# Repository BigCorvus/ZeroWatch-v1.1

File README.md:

# ZeroWatch-v1.1

**Replacement board for a cheap chinese U8/U80 watch.**  
Based on the work of Dan Geiger.
Features:<br />
- ATSAMD21 microcontroller with Arduino support via USB bootloader<br />
- capacitive touchscreen (based on the BL6280 controller)<br />
- HM11 bluetooth 4.0 module with amputated PCB antenna and primitive coax dipole instead<br />
- ST7735 128x128 18-pin SPI tft (the one that's inside the watch already)<br />
- MPU9250 9-DOF IMU<br />
- BME680 environmental sensor<br />
- vibration motor. I decided to go with https://de.aliexpress.com/item/Free-shipping-100pcs-lot-4-10-MM-Ultra-Micro-Vibration-Motor-Rotor-motor-DC-Massager-motor/32748925343.html?spm=a2g0s.9042311.0.0.27424c4dg2oSdt as the vibration motor to save space for a bigger battery.<br />
- infrared transmitter (APA3010F3C-GX LED)<br />
- piezo disc (optional)<br />
- I equipped mine with a QI inductive charging pad<br />

The software is based on Dan Geigers ingenious menu structure which enables you to add new apps easily.
It's quite raw and buggy but demonstrates most features and is optimized for power consumption. With the 403030 lipo I can get 8 days of standby time with bluetooth constantly advertising and the ATSAMD21's inbuilt RTC running.<br />

**Some tips if you want to repeat the project:**  
- The cheapest versions of the U8 (there are even ones below 10$, a great contribution to a healthy environment!) are usually so stripped-down that they are not useful anymore! They have their capacitive touch controller on the main PCB an not on a flex-rigid assembly. I found the U80 by NAIKU to be a good hacking victim. Search this on Aliexpress. Its design is slightly different to the U8 from the outside but from the inside everything fits. Note: the U8 by the same brand is useless.  
  
The pic shows some useless variants on the right and some hackable ones on the left (with their 6pin FPC connectors desoldered for the most part). As you can see,on the useless variants there's no touch controller on the ribbon cable but a 15pin FPC connector with nothing but the traces to the glass. Also, v1.0 and v1.2's bare PCB are depicted on the very left ;)  

- Finding a proper screen might be a problem. 18 pin versions of the 1.44'' ST7735/ILI9163 screen with the right dimensions are rare. In fact I've only found one source: https://de.aliexpress.com/item/Maithoga-1-44-zoll-18-PIN-SPI-TFT-LCD-St7735-Stick-IC-128RGB-128/32843155779.html?spm=a2g0s.9042311.0.0.27424c4d3j1YYo. Some screens found in the cheap U8/U80 watches have weird controller settings and dispay inverted colors or don't show the small fonts so be aware. You might need to buy several differen variants. Note: only 14 of the 18 pins have to be soldered to the PCB.  
- some modifications on the enclosure are needed. In order to accommodate the v1.1 board you have to cut away the plastic brackets that surround the microphone. This is best done usind electronics side cutters. Some other plastic tabs might need to be removed depending on the variant you have. But the enclosures are surprisingly similar with few variations between versions.  
- The button can be installed either using the native one or by installing a SW1256CT-ND switch (digikey). The latter requires some hacking to the enclosure  
- a small hole has to be drilled for the IR LED if you wish to use one.
- the HM-11 should be flashed with the newest firmware before installing on the v1.1 PCB.   
- if you have a PCB manufactured, the substrate thickness should be between 0.4 and 0.8mm, so OSH Park's 0.8mm service is a good choice.
- in the latest modification I replaced the HM11 with a tiny nRF52832 module (https://de.aliexpress.com/item/32840369737.html?spm=a2g0o.productlist.0.0.22d43589wkmK8l&s=p&algo_pvid=c23bce47-e7e4-404d-a416-df6c4eb9f3a8&algo_expid=c23bce47-e7e4-404d-a416-df6c4eb9f3a8-1&btsid=25448c7b-c97c-4e22-b295-2b7a35d97857&ws_ab_test=searchweb0_0%2Csearchweb201602_8%2Csearchweb201603_53) which I  flashed with a modified BLE UART example inside the Adafruit nRF52 core. It can be brought into sub-µA deep sleep by the ATSAMD. By using a passthrough sketch for the ATSAMD which lets it act as an USB-to UART bridge you can even program the nRF52832 via USB and the Arduino IDE. I tested the concept and it seems to be the best solution so far. Code and wiring scheme for this will be puplished as soon as I have time for it.

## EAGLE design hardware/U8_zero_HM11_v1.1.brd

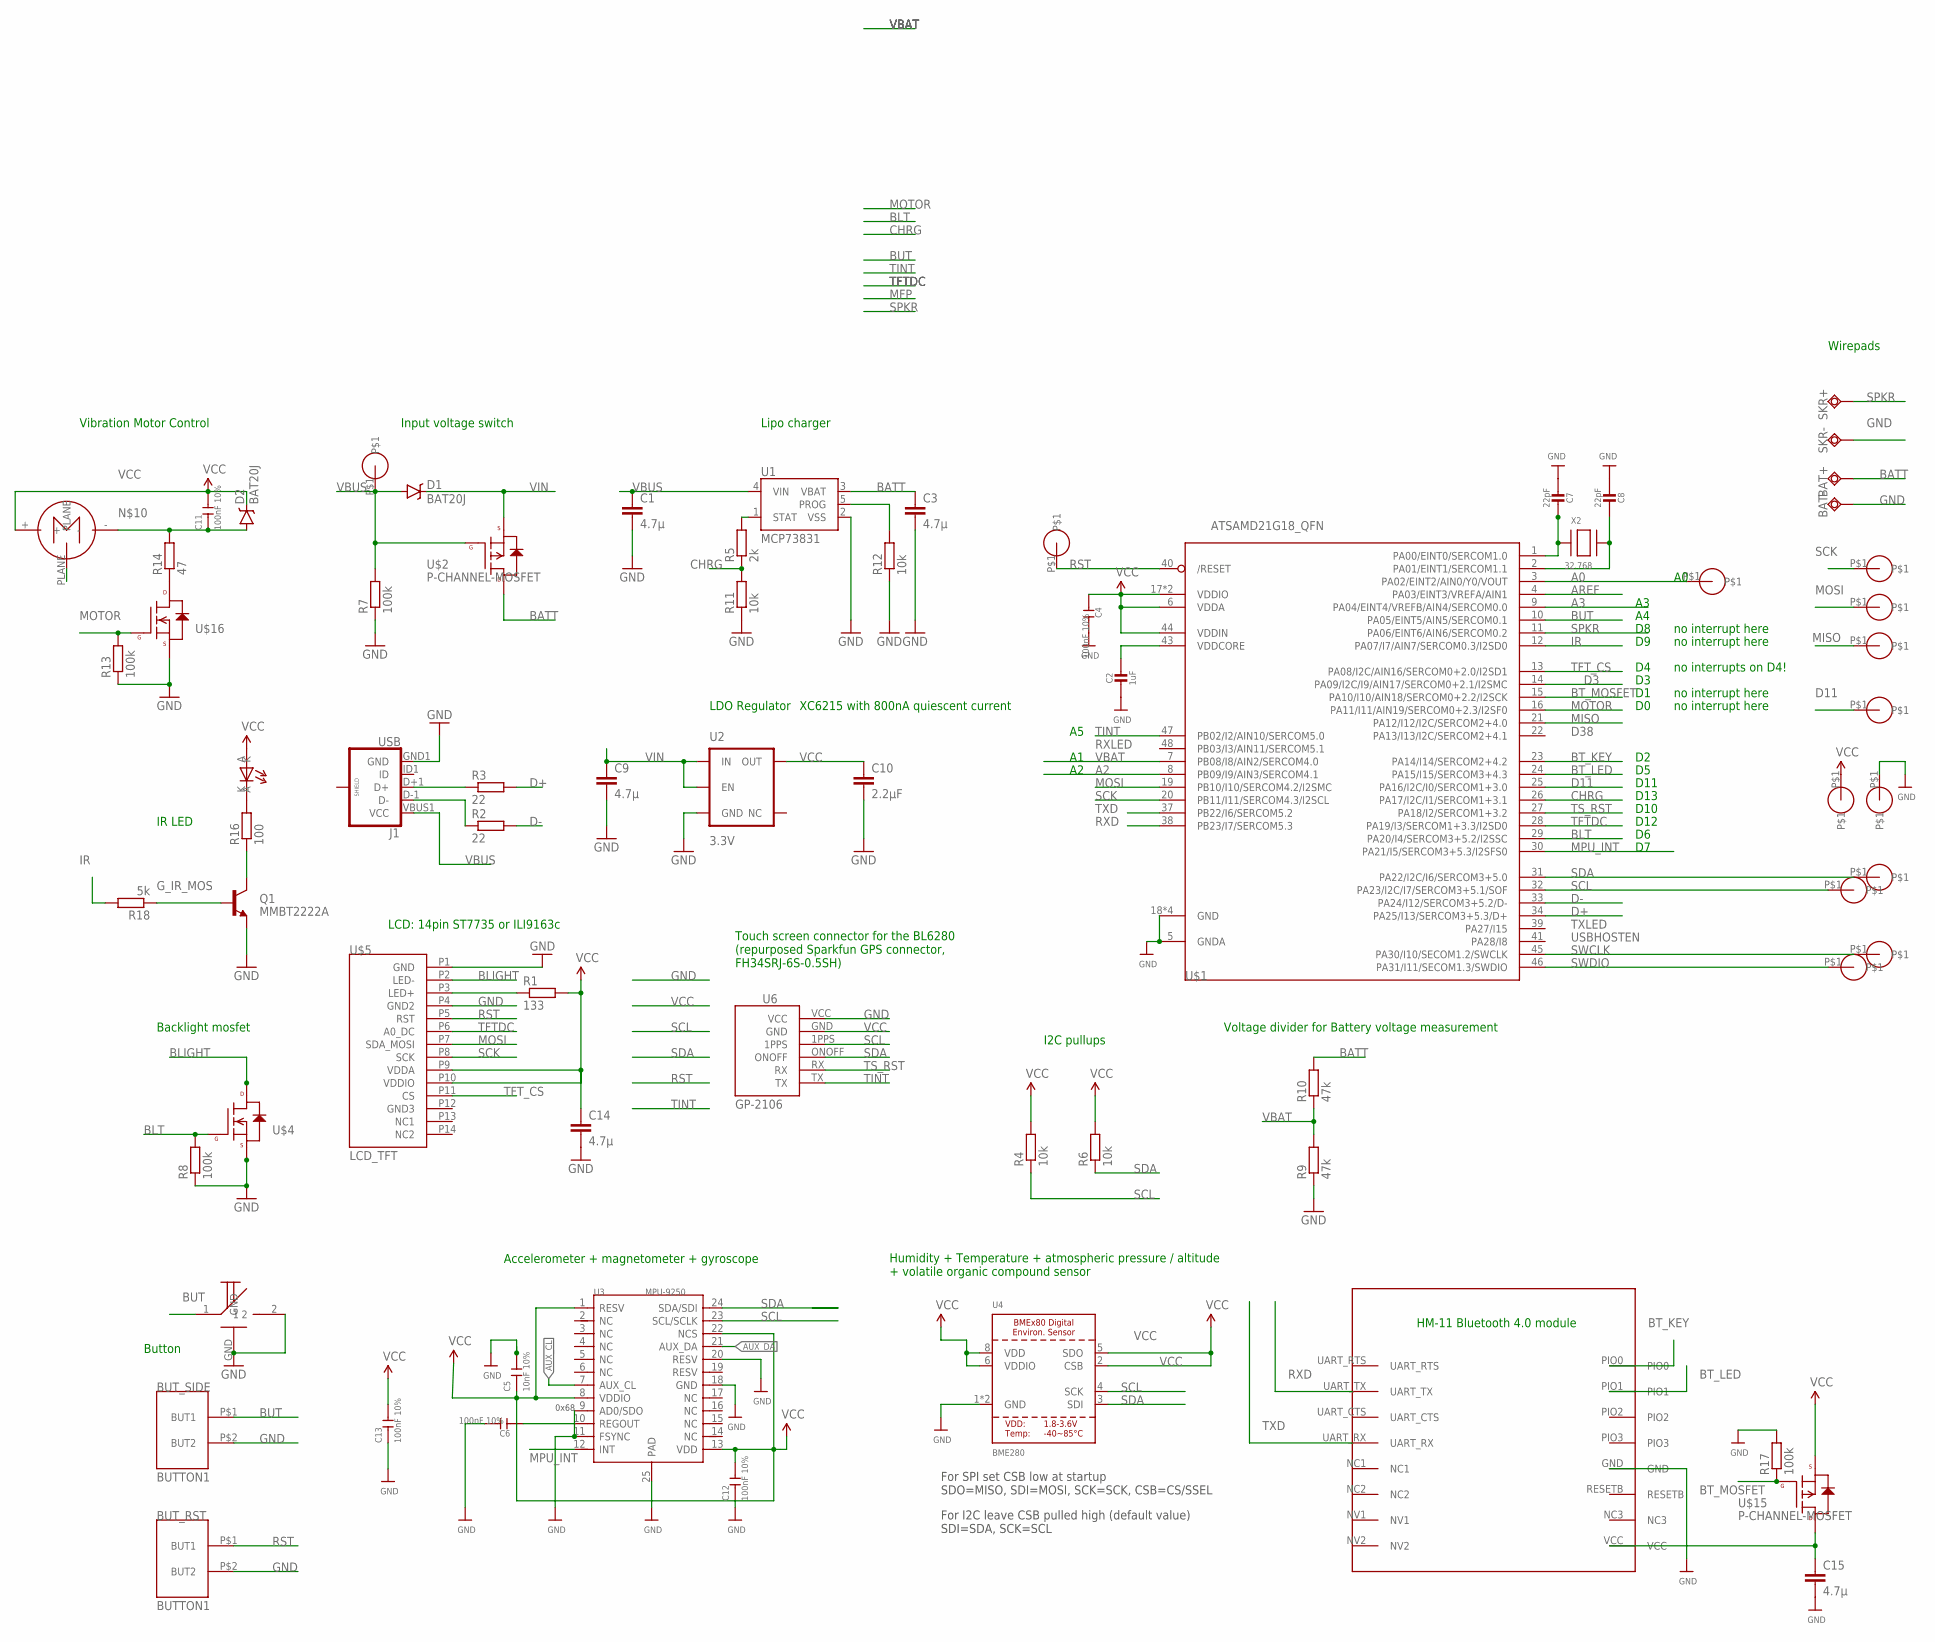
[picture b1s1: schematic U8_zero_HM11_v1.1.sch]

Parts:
BAT+: TPSQTP16R; TP16R
BAT-: TPSQTP16R; TP16R
BUT_RST: BUTTON1
BUT_SIDE: BUTTON1
C1, C3, C9, C14, C15: 4.7µ; C0603
C2: 1uF; 0603-NO
C4, C6, C11, C12, C13: 100nF 10%; C0603
C5: 10nF 10%; C0603
C7, C8: 22pF; 0603-NO
C10: 2.2µF; C0603
CLK: MINIPAD
D1, D2: BAT20J; SOD-323
DIO, DIO1, DIO2, DIO3, DIO4, DIO5: MINIPAD
J1: USB; USB-B-MICRO-SMD_V03
Q1: MMBT2222A; SOT23-3
R1: 133; R0603
R2, R3: 22; R0603
R4, R6, R11, R12: 10k; R0603
R5: 2k; R0603
R7, R8, R13, R17: 100k; R0603
R9, R10: 47k; R0603
R14: 47; R0603
R16: 100; R0603
R18: 5k; R0603
SKR+: TPSQTP12R; TP12R
SKR-: TPSQTP12R; TP12R
U1: MCP73831; SOT23-5
U2: 3.3V; SOT23-5
U3: MPU-9250; LEAD-QFN24
U4: BME280
U6: GP-2106
U$1: ATSAMD21G18_QFN; TQFN48_7MM
U$2, U$15: P-CHANNEL-MOSFET; SOT23-3
U$3, U$18, U$20, U$21, U$41, U$42: MINIPAD
U$4, U$16: N-CHANNEL-MOSFET-BSS138; SOT23-3
U$5: LCD_TFT; LCD_FPC14
U$8: HM-11
U$22: B3U-3100P-B
U$23: VIBRO
U$24: APA3010F3C-GX
X2: 32.768; XTAL3215

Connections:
A0: U$1.3 (PA02/EINT2/AIN0/Y0/VOUT), U$20.P$1
A2: U$1.8 (PB09/I9/AIN3/SERCOM4.1)
A3: U$1.9 (PA04/EINT4/VREFB/AIN4/SERCOM0.0)
AREF: U$1.4 (PA03/EINT3/VREFA/AIN1)
AUX_CL: U3.7 (AUX_CL)
AUX_DA: U3.21 (AUX_DA)
BATT: BAT+.TP, C3.1, R10.2, U1.3 (VBAT), U$2.3 (D)
BLIGHT: U$4.3 (D), U$5.P2 (LED-)
BLT: R8.2, U$1.29 (PA20/I4/SERCOM3+5.2/I2SSC), U$4.1 (G)
BT_KEY: U$1.23 (PA14/I14/SERCOM2+4.2), U$8.PIO0
BT_LED: U$1.24 (PA15/I15/SERCOM3+4.3), U$8.PIO1
BT_MOSFET: R17.1, U$1.15 (PA10/I10/AIN18/SERCOM0+2.2/I2SCK), U$15.1 (G)
BUT: BUT_SIDE.P$1 (BUT1), U$1.10 (PA05/EINT5/AIN5/SERCOM0.1), U$22.1
CHRG: R5.1, R11.2, U$1.26 (PA17/I2C/I1/SERCOM1+3.1)
D3: U$1.14 (PA09/I2C/I9/AIN17/SERCOM0+2.1/I2SMC)
D11: DIO4.P$1, U$1.25 (PA16/I2C/I0/SERCOM1+3.0)
D+: R3.2, U$1.34 (PA25/I13/SERCOM3+5.3/D+)
D-: R2.2, U$1.33 (PA24/I12/SERCOM3+5.2/D-)
GND: BAT-.TP, BUT_RST.P$2 (BUT2), BUT_SIDE.P$2 (BUT2), C1.2, C2.2, C3.2, C4.2, C5.2, C6.2, C7.2, C8.2, C9.2, C10.2, C12.1, C13.1, C14.2, C15.2, J1.GND1 (GND), Q1.2 (E), R7.1, R8.1, R9.1, R11.1, R12.1, R13.1, R17.2, SKR-.TP, U1.2 (VSS), U2.2 (GND), U3.9 (AD0/SDO), U3.11 (FSYNC), U3.18 (GND), U3.20 (RESV), U3.25 (PAD), U4.1 (GND), U4.7 (GND), U6.VCC, U$1.5 (GNDA), U$1.18 (GND), U$1.35 (GND), U$1.42 (GND), U$1.THERMAL (GND), U$4.2 (S), U$5.P1 (GND), U$5.P4 (GND2), U$8.GND, U$16.2 (S), U$22.2, U$22.GND, U$42.P$1
G_IR_MOS: Q1.1 (B), R18.1
IR: R18.2, U$1.12 (PA07/I7/AIN7/SERCOM0.3/I2SD0)
MISO: DIO1.P$1, U$1.21 (PA12/I12/I2C/SERCOM2+4.0)
MOSI: DIO2.P$1, U$1.19 (PB10/I10/SERCOM4.2/I2SMC), U$5.P7 (SDA_MOSI)
MOTOR: R13.2, U$1.16 (PA11/I11/AIN19/SERCOM0+2.3/I2SF0), U$16.1 (G)
MPU_INT: U3.12 (INT), U$1.30 (PA21/I5/SERCOM3+5.3/I2SFS0)
unnamed: C6.1, U3.10 (REGOUT)
unnamed: C7.1, U$1.1 (PA00/EINT0/SERCOM1.0), X2.P$1
unnamed: C8.1, U$1.2 (PA01/EINT1/SERCOM1.1), X2.P$2
unnamed: R14.1, U$16.3 (D)
unnamed: J1.D+1 (D+), R3.1
unnamed: J1.D-1 (D-), R2.1
unnamed: R12.2, U1.5 (PROG)
unnamed: R5.2, U1.1 (STAT)
unnamed: R1.1, U$5.P3 (LED+)
unnamed: C11.1, D2.A, R14.2, U$23.-
unnamed: Q1.3 (C), R16.1
unnamed: R16.2, U$24.K
unnamed: C15.1, U$8.VCC, U$15.3 (D)
PLANE: U$23.PLANE
RST: BUT_RST.P$1 (BUT1), U$1.40 (/RESET), U$3.P$1, U$5.P5 (RST)
RXD: U$1.38 (PB23/I7/SERCOM5.3), U$8.UART_TX
SCK: DIO3.P$1, U$1.20 (PB11/I11/SERCOM4.3/I2SCL), U$5.P8 (SCK)
SCL: R4.1, U3.23 (SCL/SCLK), U4.4 (SCK), U6.1PPS, U$1.32 (PA23/I2C/I7/SERCOM3+5.1/SOF), U$21.P$1
SDA: R6.1, U3.24 (SDA/SDI), U4.3 (SDI), U6.ONOFF, U$1.31 (PA22/I2C/I6/SERCOM3+5.0), U$18.P$1
SPKR: SKR+.TP, U$1.11 (PA06/EINT6/AIN6/SERCOM0.2)
SWCLK: CLK.P$1, U$1.45 (PA30/I10/SECOM1.2/SWCLK)
SWDIO: DIO.P$1, U$1.46 (PA31/I11/SECOM1.3/SWDIO)
TFTDC: U$1.28 (PA19/I3/SERCOM1+3.3/I2SD0), U$5.P6 (A0_DC)
TFT_CS: U$1.13 (PA08/I2C/AIN16/SERCOM0+2.0/I2SD1), U$5.P11 (CS)
TINT: U6.TX, U$1.47 (PB02/I2/AIN10/SERCOM5.0)
TS_RST: U6.RX, U$1.27 (PA18/I2/SERCOM1+3.2)
TXD: U$1.37 (PB22/I6/SERCOM5.2), U$8.UART_RX
VBAT: R9.2, R10.1, U$1.7 (PB08/I8/AIN2/SERCOM4.0)
VBUS: C1.1, D1.A, DIO5.P$1, J1.VBUS1 (VCC), R7.2, U1.4 (VIN), U$2.1 (G)
VCC: C4.1, C5.1, C10.1, C11.2, C12.2, C13.2, C14.1, D2.C, R1.2, R4.2, R6.2, U2.5 (OUT), U3.1 (RESV), U3.8 (VDDIO), U3.13 (VDD), U3.22 (NCS), U4.2 (CSB), U4.5 (SDO), U4.6 (VDDIO), U4.8 (VDD), U6.GND, U$1.6 (VDDA), U$1.17 (VDDIO), U$1.36 (VDDIO), U$1.44 (VDDIN), U$5.P9 (VDDA), U$5.P10 (VDDIO), U$15.2 (S), U$23.+, U$24.A, U$41.P$1
VDDCORE1: C2.1, U$1.43 (VDDCORE)
VIN: C9.1, D1.C, U2.1 (IN), U2.3 (EN), U$2.2 (S)

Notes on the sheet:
D38
TXLED
USBHOSTEN
RXLED
TXD
RXD
0x68
D12
D10
For SPI set CSB low at startup SDO=MISO, SDI=MOSI, SCK=SCK, CSB=CS/SSEL
For I2C leave CSB pulled high (default value) SDI=SDA, SCK=SCL
D11
D13
no interrupts on D4!
HM-11 Bluetooth 4.0 module
no interrupt here
LCD: 14pin ST7735 or ILI9163c
Touch screen connector for the BL6280 (repurposed Sparkfun GPS connector, FH34SRJ-6S-0.5SH)
Vibration Motor Control
Input voltage switch
Lipo charger
LDO Regulator
IR LED
Voltage divider for Battery voltage measurement
I2C pullups
Backlight mosfet
Button
Accelerometer + magnetometer + gyroscope
Humidity + Temperature + atmospheric pressure / altitude + volatile organic compound sensor
Wirepads
XC6215 with 800nA quiescent current

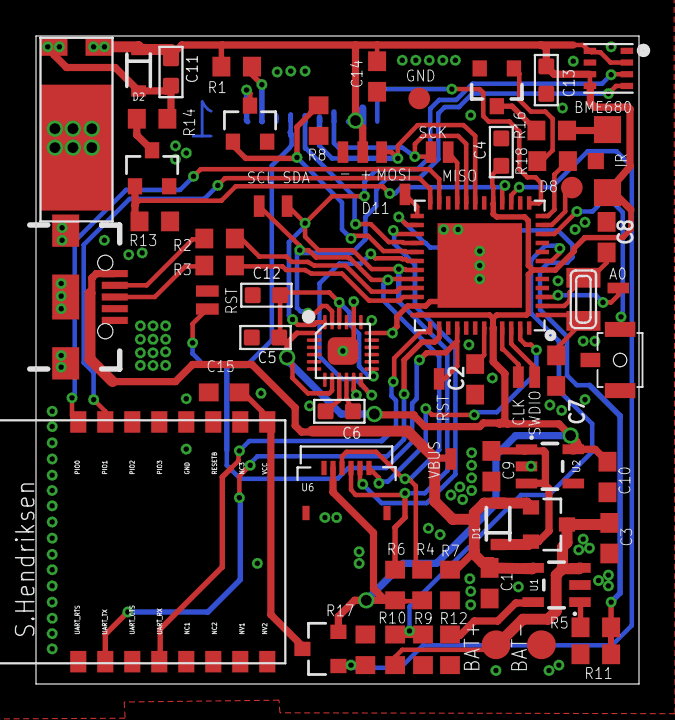
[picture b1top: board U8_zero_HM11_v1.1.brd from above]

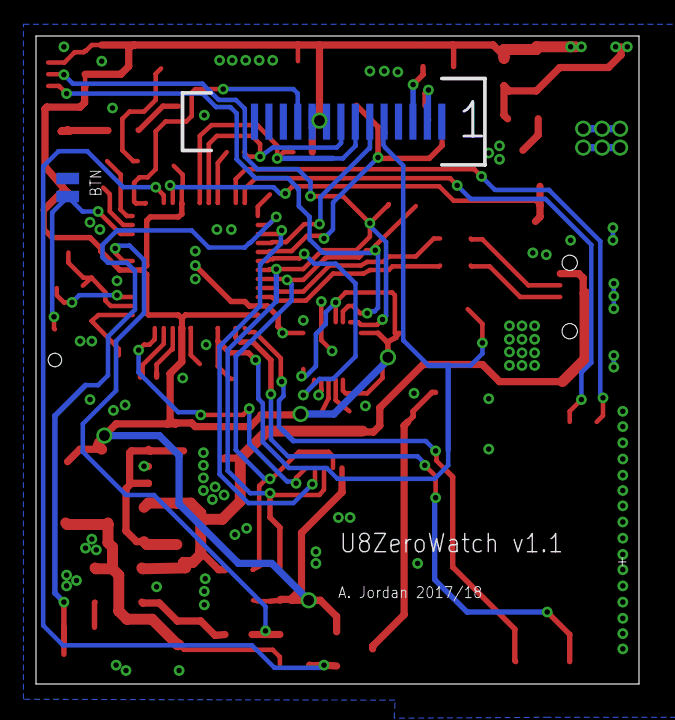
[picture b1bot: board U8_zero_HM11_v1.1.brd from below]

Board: 2 copper layers, 33.5 x 36.0 mm, 71 parts (2 on the bottom side), 50 nets.

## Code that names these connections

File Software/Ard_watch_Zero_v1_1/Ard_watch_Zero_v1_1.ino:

#include "wiring_private.h" // pinPeripheral() function
#include <Wire.h>
#include <SPI.h>
#include <Adafruit_GFX.h>    // Core graphics library
#include <Adafruit_ST7735.h> // Hardware-specific library
#include <BL6280.h>
#include <SparkFunMPU9250-DMP.h>
#include <RTCZero.h>
#include <Adafruit_Sensor.h>
#include "Adafruit_BME680.h"
//#include "ClosedCube_BME680.h"
#include <IRLibSendBase.h>    // First include the send base
//Now include only the protocols you wish to actually use.
//The lowest numbered protocol should be first but remainder 
//can be any order.
#include <IRLib_P01_NEC.h>    
#include <IRLib_P02_Sony.h>   
#include <IRLibCombo.h>     // After all protocols, include this
// All of the above automatically creates a universal sending
// class called "IRsend" containing only the protocols you want.
// Now declare an instance of that sender.
#define SEALEVELPRESSURE_HPA (1013.25)


/* Create an rtc object */
RTCZero rtc;
/* Change these values to set the current initial time */
byte seconds = 0;
byte minutes = 00;
byte hours = 00;

/* Change these values to set the current initial date */
byte Day = 24;
byte Month = 5;
byte Year = 18;

// Color definitions
#define	BLACK   0x0000
#define	BLUE    0x001F
#define	RED     0xF800
#define	GREEN   0x07E0
#define CYAN    0x07FF
#define MAGENTA 0xF81F
#define YELLOW  0xFFE0
#define WHITE   0xFFFF

#define CS 4
#define DC 12
#define BACKLIGHT 6
#define CHARGE 13
#define BUTTON A4 //A4 is  7
#define TINT A5
#define SPKR 8
#define IR 9
#define AINT 7  //MPUinterrupt
#define VBAT A1
#define MOTOR PORT_PA11
#define TS_RST 10
#define BT_CTRL 2 //formerly SD_CS
#define BT_LED 5
#define BT_MOSFET 1


unsigned long stepCount = 0;
unsigned long stepTime = 0;
unsigned long lastStepCount = 0;

//create a new SPI for SD card
//SPIClass SD_SPI (&sercom2, 3, 5, 4, SPI_PAD_0_SCK_3, SERCOM_RX_PAD_1);
//create a new I2C for sensors
//TwoWire Sens_Wire(&sercom1, 11, 13);

const uint8_t maxApp =7;
char* const appName[] = {"Clock", "Remote", "Status", "Set T", "Bright", "Test S", "Tremor", "Compass"};
MPU9250_DMP imu;
//TFT_ILI9163C tft = TFT_ILI9163C(CS, DC);
Adafruit_ST7735 tft = Adafruit_ST7735(CS,  DC, -1);
BL6280 ctp = BL6280();
Adafruit_BME680 bme; // I2C
IRsend mySender;
//ClosedCube_BME680 bme680;

volatile boolean selButton; // the Select (side) button
volatile boolean Touched;
volatile uint8_t valBright = 100;
volatile int maxX, maxY, maxZ, minX, minY, minZ;

void setup(void) {
  delay(6000); //time to program the atsamd21 before it enters sleep mode

  Wire.begin();
  Serial.begin(9600); //serial port for communication with the BT module
  pinMode(BACKLIGHT, OUTPUT);
  digitalWrite(BACKLIGHT, LOW);
  //pinMode(MOTOR, OUTPUT);
 //digitalWrite(MOTOR, LOW);
 REG_PORT_DIRSET0 = PORT_PA11 ; // Direction set to OUTPUT
 //digitalWrite(MOTOR, LOW);
   REG_PORT_OUTCLR0 = PORT_PA11 ; // set state of pin(s) to LOW
  pinMode(BT_MOSFET, OUTPUT);
  digitalWrite(BT_MOSFET, LOW);
   pinMode(TS_RST, OUTPUT);
  digitalWrite(TS_RST, HIGH);
  pinMode(CHARGE, INPUT);
  pinMode(TINT, INPUT);
  pinMode(SPKR, OUTPUT);
  pinMode(BT_CTRL, OUTPUT);
  digitalWrite(BT_CTRL, HIGH);
  digitalWrite(SPKR, LOW);
  pinMode(AINT, INPUT_PULLUP);
pinMode(BUTTON, INPUT_PULLUP);
  attachInterrupt(BUTTON, btn_isr, LOW);//LOW is needed here in order to be able to wake the atsamd21 from deep sleep!!!!!!!!
  //attachInterrupt(AINT, mpu_isr, LOW);
 //attachInterrupt(TINT, touch_isr, CHANGE);//attachInterrupt(EXTERNAL_INT_6, ISR, FALLING);
  // Configure the regulator to run in normal mode when in standby mode
  // Otherwise it defaults to low power mode and can only supply 50 uA
  //SYSCTRL->VREG.bit.RUNSTDBY = 1;

  // Enable the DFLL48M clock in standby mode
  //SYSCTRL->DFLLCTRL.bit.RUNSTDBY = 1;
  // Set the EIC (External Interrupt Controller) to wake up the MCU
  // on an external interrupt from digital pin 0. (It's EIC channel 11)
  //EIC->WAKEUP.reg = EIC_WAKEUP_WAKEUPEN5;
  
  // Disable the USB device, this avoids USB interrupts
  // mainly the SOF every 1ms.
  // Note: you'll have to double tap the reset button to load new sketches
  //USBDevice.detach();
  rtc.begin(); //Start RTC library, this is where the clock source is initialized
  // Set the time
  rtc.setHours(hours);
  rtc.setMinutes(minutes);
  rtc.setSeconds(seconds);
  // Set the date
  rtc.setDay(Day);
  rtc.setMonth(Month);
  rtc.setYear(Year);
  rtc.setAlarmTime(00, 00, 10); //set alarm time to go off in 10 seconds
  //rtc.enableAlarm(rtc.MATCH_HHMMSS); //set alarm
  // rtc.attachInterrupt(ding); //creates an interrupt that wakes the SAMD21 which is triggered by a FTC alarm 
  tft.initR(INITR_GREENTAB);
  tft.setRotation(0);
  tft.setTextColor(WHITE, BLACK);
  backLight(0);
  selButton = false;
  Touched = false;
  BTwake();
  BTsetup();
 
//basicIMUsetup();
   
//basicBMEsetup();  
 
  
   ctp.begin();
   

  tone(SPKR, 1000, 200);
vibrate();


  //rtc.setAlarmTime(00, 00, 10); //set alarm time to go off in 10 seconds

  //following two lines enable alarm, comment both out if you want to do external interrupt
  // rtc.enableAlarm(rtc.MATCH_HHMMSS); //set alarm
  //rtc.attachInterrupt(ding); //creates an interrupt that wakes the SAMD21 which is triggered by a FTC alarm
  // attachInterrupt(BUTTON, ISR, LOW);
  //comment out the below line if you are using RTC alarm for interrupt
  //extInterrupt(A1); //creates an interrupt source on external pin
}

void loop() {

  modeSleep(); // Shutdown systems for sleep
  //  sleep_mode(); // go to sleep
 // rtc.standbyMode(); //library call
  samSleep();
  modeWake();

  delay(300); //debounce
  selButton = false;
  backLight(valBright);
  appClock();
  unsigned long timer1 = millis() + 5000; //Display stays on 5 seconds
  uint8_t sApp = 0;

  while (millis() < timer1) {
    if ( selButton == true) {
      tone(SPKR, 2000, 70);
      delay(100); //debounce
      selButton = false;
    }
    //Look for the gesture
    if (ctp.touched()) {
      //Touched = false;
      sApp = appMenu();
      //appName[] = {"Clock", "Remote", "Status", "Set T", "Bright", "Test S", "Tremor", "Compass"};
      switch (sApp) {
        case 0:
          timer1 = millis() + 5000;
          appClock();
          break;
        case 1:
          appRemote();
          break;
        case 2:
          appStatus();
          break;
        case 3:
          appSetTime();
          break;
        case 4:
          appSetBright();
          break;
        case 5:
          appTestS();
          break;
        case 6:
          appTremor();
          break;
        case 7:
          appCompass();
          break;
      }
    }
    if(digitalRead(TINT)==LOW){
      //tone(SPKR,1000,20);
    }
  }

  tft.fillScreen(BLACK);
  backLight(0);
  delay(5);

}

void btn_isr()
{
  selButton = true;
  //backLight(0);
  
}

void touch_isr()
{
  //tone(SPKR,1000,20);
  //if(ctp.touched())
  //Touched = true;
  //selButton = true;
  //backLight(0);
}

void mpu_isr()
{
   
}

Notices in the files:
parts and their libraries:
SparkFun-DiscreteSemi: Licensing: Creative Commons ShareAlike 4.0 International - https://creativecommons.org/licenses/by-sa/4.0
microbuilder: This work is placed in the public domain, and may be freely used for commercial and non-commercial work with the following conditions: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
